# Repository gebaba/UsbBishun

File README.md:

# 带笔画输入法的键盘

1 横/提<br />
2 竖/竖钩<br />
3 撇<br />
4 捺/点<br />
5 折<br />
6 回退/清除<br />
7 确定/模式<br />
8 上翻/放大<br />
9 下翻/缩小<br />

# 第一版问题

W26Q16 存储器和 STM32F103C8T6 的 SPI1 接口错误 PA6/PA7 颠倒<br />
复位按键封装过小<br />
USB 口 500mA 电阻封装过小<br />
按键和 LCD 的接口根据布线进行调整<br />
屏幕灯的封装过小<br />
32769 晶震处过孔<br />

外壳液晶屏位置调整<br />
外壳腔体高度过低需要留有一定余量<br />

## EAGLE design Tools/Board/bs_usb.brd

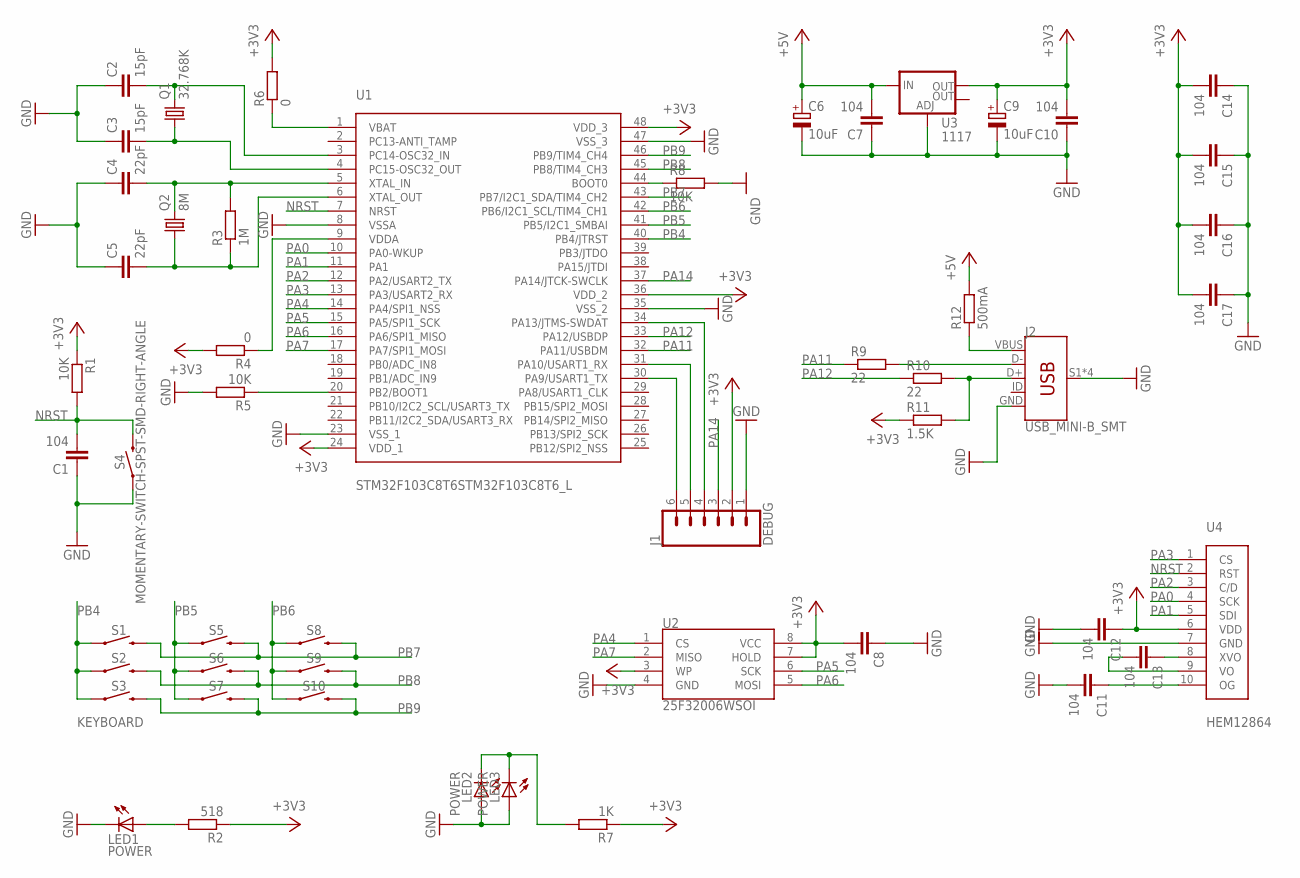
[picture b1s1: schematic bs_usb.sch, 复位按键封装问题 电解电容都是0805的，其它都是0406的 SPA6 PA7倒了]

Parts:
C1, C7, C8, C10, C11, C12, C13, C14, C15, C16, C17: 104; C0603
C2, C3: 15pF; C0603
C4, C5: 22pF; C0603
C6, C9: 10uF; A/3216-18R
J1: DEBUG; 1X06_NO_SILK
J2: USB_MINI-B_SMT; USB-MINIB
LED1, LED2, LED3: POWER; CHIP-LED0805
Q1: 32.768K; TC26H
Q2: 8M; SM49
R1, R5, R8: 10K; R0603
R2: 518; R0603
R3: 1M; R0603
R4, R6: 0; R0603
R7: 1K; R0603
R9, R10: 22; R0603
R11: 1.5K; R0603
R12: 500mA; R0603
S1, S2, S3, S5, S6, S7, S8, S9, S10: MOMENTARY-SWITCH-SPST-PTH-6.0MM; TACTILE_SWITCH_PTH_6.0MM
S4: MOMENTARY-SWITCH-SPST-SMD-RIGHT-ANGLE; TACTILE_SWITCH_SMD_RIGHT_ANGLE
U1: STM32F103C8T6STM32F103C8T6_L; TQFP48_7X7
U2: 25F32006WSOI; SO08-EIAJ
U3: 1117; SOT223
U4: HEM12864

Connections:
+3V3: C8.2, C9.+, C10.2, C12.1, C14.2, C15.2, C16.2, C17.2, J1.2, R1.1, R2.1, R4.2, R6.2, R7.1, R11.1, U1.24 (VDD_1), U1.36 (VDD_2), U1.48 (VDD_3), U2.3 (WP), U2.7 (HOLD), U2.8 (VCC), U3.2 (OUT), U4.6 (VDD)
+5V: C6.+, C7.2, R12.2, U3.3 (IN)
GND: C1.1, C2.1, C3.1, C4.1, C5.1, C6.-, C7.1, C8.1, C9.-, C10.1, C11.2, C12.2, C14.1, C15.1, C16.1, C17.1, J1.1, J2.GND, J2.S1 (SHIELD), J2.S2 (SHIELD), J2.S3 (SHIELD), J2.S4 (SHIELD), LED1.C, LED2.A, LED3.A, R5.2, R8.2, S4.1, U1.8 (VSSA), U1.23 (VSS_1), U1.35 (VSS_2), U1.47 (VSS_3), U2.4 (GND), U3.1 (ADJ), U4.7 (GND)
unnamed: R8.1, U1.44 (BOOT0)
unnamed: R6.1, U1.1 (VBAT)
unnamed: R5.1, U1.20 (PB2/BOOT1)
unnamed: R4.1, U1.9 (VDDA)
unnamed: C4.2, Q2.2, R3.2, U1.5 (XTAL_IN)
unnamed: C2.2, Q1.2, U1.3 (PC14-OSC32_IN)
unnamed: C5.2, Q2.1, R3.1, U1.6 (XTAL_OUT)
unnamed: C3.2, Q1.1, U1.4 (PC15-OSC32_OUT)
unnamed: J2.D-, R9.2
unnamed: J2.D+, R10.2, R11.2
unnamed: J2.VBUS, R12.1
unnamed: J1.6, U1.30 (PA9/USART1_TX)
unnamed: J1.5, U1.31 (PA10/USART1_RX)
unnamed: C13.1, U4.8 (XVO)
unnamed: C13.2, U4.9 (VO)
unnamed: C11.1, U4.10 (OG)
unnamed: LED2.C, LED3.C, R7.2
unnamed: LED1.A, R2.2
NRST: C1.2, R1.2, S4.2, U1.7 (NRST), U4.2 (RST)
PA0: U1.10 (PA0-WKUP), U4.4 (SCK)
PA1: U1.11 (PA1), U4.5 (SDI)
PA2: U1.12 (PA2/USART2_TX), U4.3 (C/D)
PA3: U1.13 (PA3/USART2_RX), U4.1 (CS)
PA4: U1.14 (PA4/SPI1_NSS), U2.1 (CS)
PA5: U1.15 (PA5/SPI1_SCK), U2.6 (SCK)
PA6: U1.16 (PA6/SPI1_MISO), U2.5 (MOSI)
PA7: U1.17 (PA7/SPI1_MOSI), U2.2 (MISO)
PA11: R9.1, U1.32 (PA11/USBDM)
PA12: R10.1, U1.33 (PA12/USBDP)
PA13: J1.4, U1.34 (PA13/JTMS-SWDAT)
PA14: J1.3, U1.37 (PA14/JTCK-SWCLK)
PB4: S1.1, S2.1, S3.1, U1.40 (PB4/JTRST)
PB5: S5.1, S6.1, S7.1, U1.41 (PB5/I2C1_SMBAI)
PB6: S8.1, S9.1, S10.1, U1.42 (PB6/I2C1_SCL/TIM4_CH1)
PB7: S1.3 (2), S5.3 (2), S8.3 (2), U1.43 (PB7/I2C1_SDA/TIM4_CH2)
PB8: S2.3 (2), S6.3 (2), S9.3 (2), U1.45 (PB8/TIM4_CH3)
PB9: S3.3 (2), S7.3 (2), S10.3 (2), U1.46 (PB9/TIM4_CH4)

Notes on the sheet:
KEYBOARD

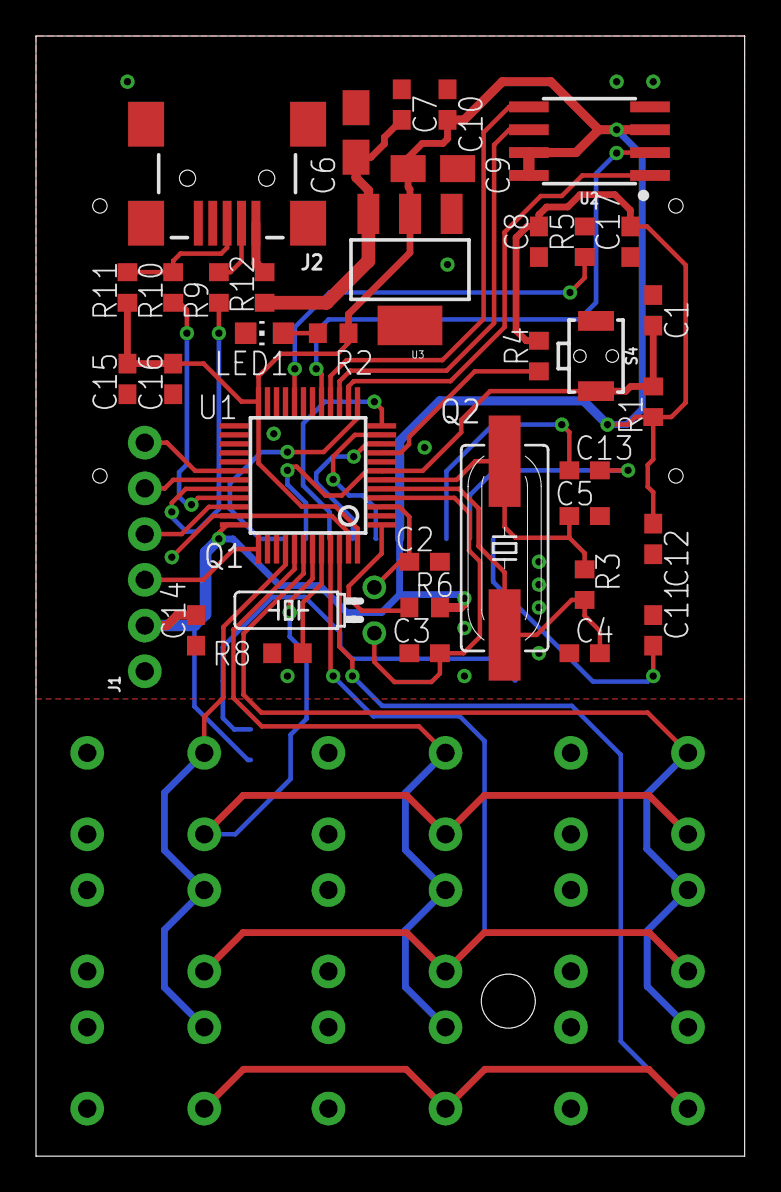
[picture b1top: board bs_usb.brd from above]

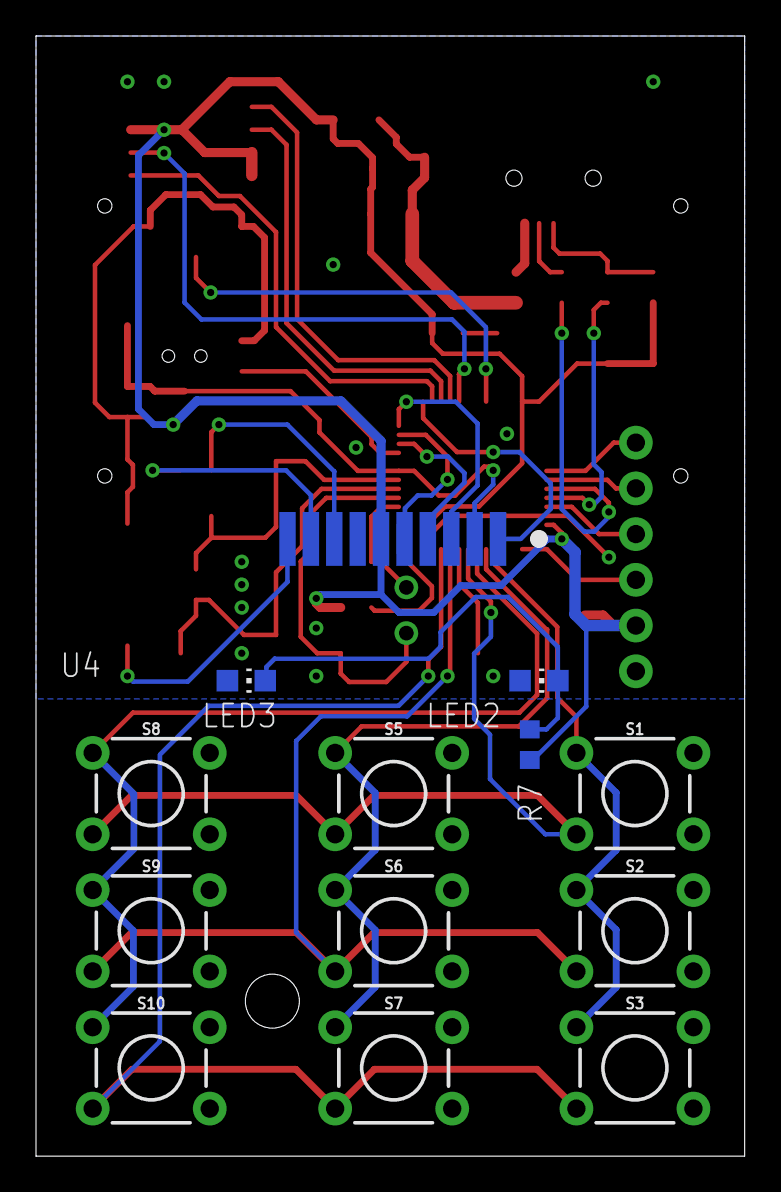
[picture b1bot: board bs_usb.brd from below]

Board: 2 copper layers, 39.4 x 62.2 mm, 50 parts (13 on the bottom side), 40 nets.

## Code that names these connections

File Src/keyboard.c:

/**
 * PB4 PB5 PB6 PB7 PB8 PB9
 * 
 * 
 */
#include "keyboard.h"
#include "missing.h"

#include "stm32f10x_conf.h"

/**
 * 扫描键盘
 * 
 * 
 */
static int read(void) {
    GPIO_ResetBits(GPIOB, GPIO_Pin_4);
    GPIO_SetBits(GPIOB, GPIO_Pin_5);
    GPIO_SetBits(GPIOB, GPIO_Pin_6);
    if (!GPIO_ReadInputDataBit(GPIOB, GPIO_Pin_7)) {
        return KEY_P;
    } else if (!GPIO_ReadInputDataBit(GPIOB, GPIO_Pin_8)) {
        return KEY_DELETE;
    } else if (!GPIO_ReadInputDataBit(GPIOB, GPIO_Pin_9)) {
        return KEY_NEXT;
    }
    GPIO_SetBits(GPIOB, GPIO_Pin_4);
    GPIO_ResetBits(GPIOB, GPIO_Pin_5);
    GPIO_SetBits(GPIOB, GPIO_Pin_6);
    if (!GPIO_ReadInputDataBit(GPIOB, GPIO_Pin_7)) {
        return KEY_S;
    } else if (!GPIO_ReadInputDataBit(GPIOB, GPIO_Pin_8)) {
        return KEY_Z;
    } else if (!GPIO_ReadInputDataBit(GPIOB, GPIO_Pin_9)) {
        return KEY_PREVIOUS;
    }
    GPIO_SetBits(GPIOB, GPIO_Pin_4);
    GPIO_SetBits(GPIOB, GPIO_Pin_5);
    GPIO_ResetBits(GPIOB, GPIO_Pin_6);
    if (!GPIO_ReadInputDataBit(GPIOB, GPIO_Pin_7)) {
        return KEY_H;
    } else if (!GPIO_ReadInputDataBit(GPIOB, GPIO_Pin_8)) {
        return KEY_N;
    } else if (!GPIO_ReadInputDataBit(GPIOB, GPIO_Pin_9)) {
        return KEY_OK;
    }
    wait(80);
    return -1;
}

/**
 * 读取按键（阻塞）
 *  
 * return: 按键值
 * 
 */
int readKey(void) {
    int key;
    int i = 0;
    while ((key = read()) == -1);
    do {
        if (i < 9) {
            i++;
        } else {
            switch (key) {
            case KEY_DELETE:
                key = KEY_CLEAR;
                break;
            case KEY_OK:
                key = KEY_MODE;
                break;
            case KEY_PREVIOUS:
                key = KEY_ZOOMOUT;
                break;
            case KEY_NEXT:
                key = KEY_ZOOM;
                break;
            }
            while (read() != -1);
            break;
        }
        wait(80);
    } while (read() != -1);
    return key;
}

/**
 * 初始化 
 * 
 */
void initializeKey(void) {
    RCC_APB2PeriphClockCmd(
        RCC_APB2Periph_GPIOB,
        ENABLE
    );
    /**
     * PB4/JTRST 需要复用
     * 
     * 
     */
    RCC_APB2PeriphClockCmd(RCC_APB2Periph_AFIO, ENABLE);
    GPIO_PinRemapConfig(GPIO_Remap_SWJ_NoJTRST, ENABLE);
    {
        GPIO_InitTypeDef GPIO_InitStruct;
        GPIO_InitStruct.GPIO_Pin = GPIO_Pin_4 | GPIO_Pin_5 | GPIO_Pin_6;
        GPIO_InitStruct.GPIO_Speed = GPIO_Speed_50MHz;
        GPIO_InitStruct.GPIO_Mode = GPIO_Mode_Out_PP;
        GPIO_Init(GPIOB, &GPIO_InitStruct);
        GPIO_InitStruct.GPIO_Pin = GPIO_Pin_7 | GPIO_Pin_8 | GPIO_Pin_9;
        GPIO_InitStruct.GPIO_Mode = GPIO_Mode_IPU;
        GPIO_Init(GPIOB, &GPIO_InitStruct);
    }
}

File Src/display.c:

#include "display.h"
#include "missing.h"

#include "stm32f10x_conf.h"

/**
 * 引脚 PA0 PA1 PA2 PA3
 * 
 * 
 */
#define	SEL_SET GPIO_SetBits(GPIOA, GPIO_Pin_3)
#define	SEL_CLR GPIO_ResetBits(GPIOA, GPIO_Pin_3)
#define	DAT_SET	GPIO_SetBits(GPIOA, GPIO_Pin_2)
#define	DAT_CLR	GPIO_ResetBits(GPIOA, GPIO_Pin_2)
#define	SDI_SET	GPIO_SetBits(GPIOA, GPIO_Pin_1)
#define	SDI_CLR	GPIO_ResetBits(GPIOA, GPIO_Pin_1)
#define	SCK_SET	GPIO_SetBits(GPIOA, GPIO_Pin_0)
#define	SCK_CLR	GPIO_ResetBits(GPIOA, GPIO_Pin_0)

/**
 * 向LCD发送
 * 
 * data: 发送的数据
 * 
 * 
 */
static void send(char data) {
    int i;
    for (i = 0; i < 8; i++) {
        SCK_CLR;
        if(data & 0x80) {
            SDI_SET;
        } else {
            SDI_CLR;
        }
        SCK_SET;
        data <<= 1;
    }
}

/**
 * 发送指令
 * 
 * command: 指令
 * 
 */
static void sendCommand(char command) {
    SEL_CLR;
    DAT_CLR;
    send(command);
    SEL_SET;
}

/**
 * 发送数据
 * 
 * data: 发送的数据
 * 
 */
static void sendData(char data) {
    SEL_CLR;
    DAT_SET;
    send(data);
    SEL_SET;
}

/**
 * 屏幕初始化
 * 
 * 
 */
void initializeLcd(void) {
	RCC_APB2PeriphClockCmd(RCC_APB2Periph_GPIOA, ENABLE);
	{
		GPIO_InitTypeDef GPIO_InitStruct;
		GPIO_InitStruct.GPIO_Pin = GPIO_Pin_3 | GPIO_Pin_2 | GPIO_Pin_1 | GPIO_Pin_0;
		GPIO_InitStruct.GPIO_Mode = GPIO_Mode_Out_PP;
		GPIO_InitStruct.GPIO_Speed = GPIO_Speed_50MHz;
		GPIO_Init(GPIOA, &GPIO_InitStruct);
	}
	GPIO_SetBits(GPIOA, GPIO_Pin_3 | GPIO_Pin_2 | GPIO_Pin_1 | GPIO_Pin_0);
	sendCommand(0xe2);
	wait(100);
	sendCommand(0xa0);
	sendCommand(0xc8);
	sendCommand(0xa2);
	sendCommand(0x2f);
	sendCommand(0x25);
	sendCommand(0x81);
	sendCommand(0x19);
	sendCommand(0x40);
	sendCommand(0xaf);
	draw(0);
}

/**
 * 显示图像
 * 
 * data: 整屏数据
 * 
 */
void draw(char *data) {
    int i;
    int j;
	for(i = 0; i < ROW_MAX; i++) {
		sendCommand(0xb0 + i);
		sendCommand(0x10);
		sendCommand(0x00);
		for(j = 0; j < COL_MAX; j++) {
			sendData(data ? data[i + j * ROW_MAX] : 0x00);
		}
	}
}

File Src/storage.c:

/**
 * 引脚 PA4 PA5 PA6 PA7[SPI1]
 * 
 * 
 */
#include "storage.h"

#include "stm32f10x_conf.h"

#define	SEL_SET GPIO_SetBits(GPIOA, GPIO_Pin_4)
#define	SEL_CLR GPIO_ResetBits(GPIOA, GPIO_Pin_4)

#ifndef USE_SPI1

#define	SCK_SET GPIO_SetBits(GPIOA, GPIO_Pin_5)
#define	SCK_CLR GPIO_ResetBits(GPIOA, GPIO_Pin_5)
#define	SDO_SET GPIO_SetBits(GPIOA, GPIO_Pin_6)
#define	SDO_CLR GPIO_ResetBits(GPIOA, GPIO_Pin_6)
#define	SDI_GET GPIO_ReadInputDataBit(GPIOA, GPIO_Pin_7)

#endif

/**
 * 发送或者接收数据
 * 
 * data: DUMMY-0xA5 要发送的数据
 * 
 * return: 接收到的数据
 * 
 */
static char send(char data) {
#ifndef USE_SPI1
    int r = 0;
    int i;
    for (i = 0; i < 8; i++) {
        SCK_CLR;
        if (data & 0x80) {
            SDO_SET;
        } else {
            SDO_CLR;
        }
        data <<= 1;
        SCK_SET;
        r <<= 1;
        if (SDI_GET) {
            r |= 1;
        }
        SCK_CLR;
    }
    return r;
#else
    while (SPI_I2S_GetFlagStatus(
        SPI1,
        SPI_I2S_FLAG_TXE
    ) == RESET);
    SPI_I2S_SendData(SPI1, data);
    while (SPI_I2S_GetFlagStatus(SPI1, SPI_I2S_FLAG_RXNE) == RESET);
    return SPI_I2S_ReceiveData(SPI1);
#endif
}

/**
 * 初始化
 * 
 * return: JEDEC ID 
 * 
 */
int initializeSpi(void) {
    int id;
    RCC_APB2PeriphClockCmd(
        RCC_APB2Periph_GPIOA,
        ENABLE
    );
#ifndef USE_SPI1
    {
        GPIO_InitTypeDef GPIO_InitStruct;
        GPIO_InitStruct.GPIO_Pin = GPIO_Pin_4 | GPIO_Pin_5 | GPIO_Pin_6;
        GPIO_InitStruct.GPIO_Speed = GPIO_Speed_50MHz;
        GPIO_InitStruct.GPIO_Mode = GPIO_Mode_Out_PP;
        GPIO_Init(GPIOA, &GPIO_InitStruct);
        GPIO_InitStruct.GPIO_Pin = GPIO_Pin_7;
        GPIO_InitStruct.GPIO_Mode = GPIO_Mode_IPU;
        GPIO_Init(GPIOA, &GPIO_InitStruct);
    }
#else
    RCC_APB2PeriphClockCmd(RCC_APB2Periph_SPI1, ENABLE);
    RCC_APB2PeriphClockCmd(RCC_APB2Periph_AFIO, ENABLE);
    {
        GPIO_InitTypeDef GPIO_InitStruct;
        GPIO_InitStruct.GPIO_Pin = GPIO_Pin_5 | GPIO_Pin_6 | GPIO_Pin_7;
        GPIO_InitStruct.GPIO_Speed = GPIO_Speed_50MHz;
        GPIO_InitStruct.GPIO_Mode = GPIO_Mode_AF_PP;
        GPIO_Init(GPIOA, &GPIO_InitStruct);
        GPIO_InitStruct.GPIO_Pin = GPIO_Pin_4;
        GPIO_InitStruct.GPIO_Mode = GPIO_Mode_Out_PP;
        GPIO_Init(GPIOA, &GPIO_InitStruct);
    }
    {
        SPI_InitTypeDef SPI_InitStruct;
        SPI_InitStruct.SPI_Direction = SPI_Direction_2Lines_FullDuplex;
        SPI_InitStruct.SPI_Mode = SPI_Mode_Master;
        SPI_InitStruct.SPI_DataSize = SPI_DataSize_8b;
        SPI_InitStruct.SPI_CPOL = SPI_CPOL_High;
        SPI_InitStruct.SPI_CPHA = SPI_CPHA_2Edge;
        SPI_InitStruct.SPI_NSS = SPI_NSS_Soft;
        SPI_InitStruct.SPI_BaudRatePrescaler = SPI_BaudRatePrescaler_32;
        SPI_InitStruct.SPI_FirstBit = SPI_FirstBit_MSB;
        SPI_InitStruct.SPI_CRCPolynomial = 7;
        SPI_Init(SPI1, &SPI_InitStruct);
        SPI_Cmd(SPI1, ENABLE);
    }
#endif
    SEL_SET;
    SEL_CLR;
    send(0x9f);
    id = (send(0xff) << 16) | (send(0xff) << 8) | (send(0xff));
    SEL_SET;
    return id;
}

/**
 * 读数据
 * 
 * buf: 数据缓冲区
 * bufSize: 缓冲区大小
 * startAddress: 起始地址
 * 
 * return: 读到的数量
 * 
 */
int receiveData(char *buf, int bufSize, int startAddress) {
    int i;
    SEL_CLR;
    send(0x03);
    send((startAddress & 0xff0000) >> 16);
    send((startAddress & 0xff00) >> 8);
    send((startAddress & 0xff));
    for (i =  0; i < bufSize; i++) {
        buf[i] = send(0xff);
    }
    SEL_SET;
    return bufSize;
}

/**
 * 写数据
 * 
 * buf: 数据缓冲区
 * bufSize: 缓冲区大小
 * startAddress: 起始地址
 * 
 * return: 写入的数量
 * 
 */
int sendData(char *buf, int bufSize, int startAddress) {
    int i;
    SEL_CLR;
    send(0x06);
    SEL_SET;
    /**
     * 写使能
     * 
     * 
     */
    SEL_CLR;
    send(0x02);
    send((startAddress & 0xFF0000) >> 16);
    send((startAddress & 0xFF00) >> 8);  
    send((startAddress & 0xFF));
    for (i =  0; i < bufSize; i++) {
        send(buf[i]);
    }
    SEL_SET;
    /**
     * 等待写结束
     * 
     * 
     */
    SEL_CLR;
    send(0x05);
    while (send(0xff) & 0x01);
    SEL_SET;
    return bufSize;
}


/**
 * 块擦除
 * 
 * startAddress: 起始地址
 * 
 * return: 擦除大小
 * 
 */
int erase(int startAddress) {
    SEL_CLR;
    send(0x06);
    SEL_SET;
    SEL_CLR;
    send(0x01);
    send(0x00);
    send(0x00);
    SEL_SET;
    SEL_CLR;
    send(0x05);
    while (send(0xff) & 0x01);
    SEL_SET;
    /**
     * 擦除之前要清除写保护状态
     * 
     * 
     */
    SEL_CLR;
    send(0x06);
    SEL_SET;
    SEL_CLR;
    send(0x20);
    send((startAddress & 0xFF0000) >> 16);
    send((startAddress & 0xFF00) >> 8);  
    send((startAddress & 0xFF));
    SEL_SET;

    SEL_CLR;
    send(0x05);
    while (send(0xff) & 0x01);
    SEL_SET;
    return 4096;
}

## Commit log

2019-01-16 1. release

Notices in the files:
parts and their libraries:
SparkFun-Connectors: Licensing: Creative Commons ShareAlike 4.0 International - https://creativecommons.org/licenses/by-sa/4.0
